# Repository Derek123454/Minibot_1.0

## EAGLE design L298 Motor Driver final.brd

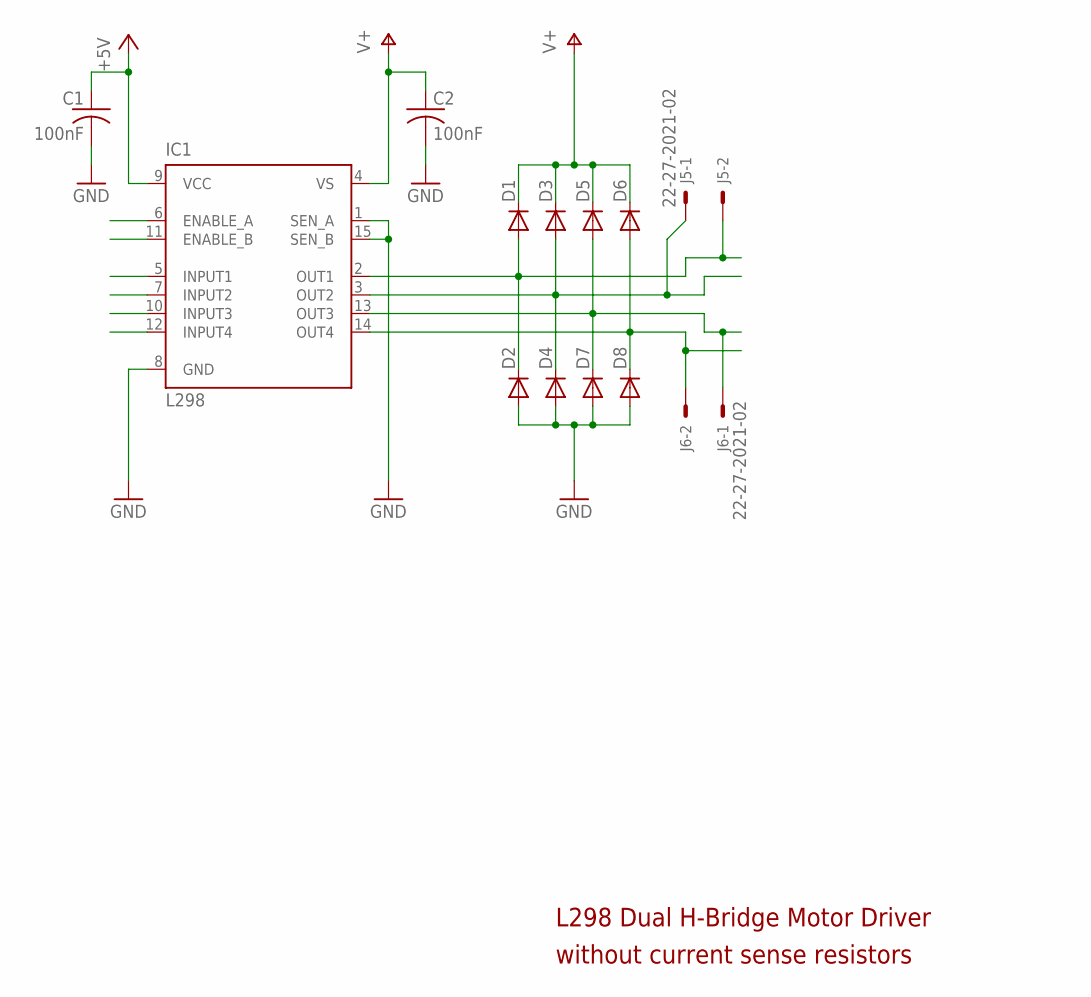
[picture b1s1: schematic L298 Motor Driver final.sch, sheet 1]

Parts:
C1, C2: 100nF; C050-024X044
D1, D2, D3, D4, D5, D6, D7, D8: DIODE-D-5; D-5
IC1: L298; MULTIWATT-15
J5, J6: 22-27-2021-02; 6410-02

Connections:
+5V: C1.1, IC1.9 (VCC); also elsewhere on the board
GND: C1.2, C2.2, D2.A, D4.A, D7.A, D8.A, IC1.1 (SEN_A), IC1.8 (GND), IC1.15 (SEN_B); also elsewhere on the board
GPIO12: IC1.6 (ENABLE_A); also elsewhere on the board
GPIO16: IC1.11 (ENABLE_B); also elsewhere on the board
GPIO19: IC1.12 (INPUT4); also elsewhere on the board
GPIO20: IC1.5 (INPUT1); also elsewhere on the board
GPIO21: IC1.7 (INPUT2); also elsewhere on the board
GPIO26: IC1.10 (INPUT3); also elsewhere on the board
unnamed: D1.A, D2.C, IC1.2 (OUT1), J5.2
unnamed: D3.A, D4.C, IC1.3 (OUT2), J5.1
unnamed: D6.A, D8.C, IC1.14 (OUT4), J6.2
unnamed: D5.A, D7.C, IC1.13 (OUT3), J6.1
V+: C2.1, D1.C, D3.C, D5.C, D6.C, IC1.4 (VS); also elsewhere on the board

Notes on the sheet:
L298 Dual H-Bridge Motor Driver
without current sense resistors

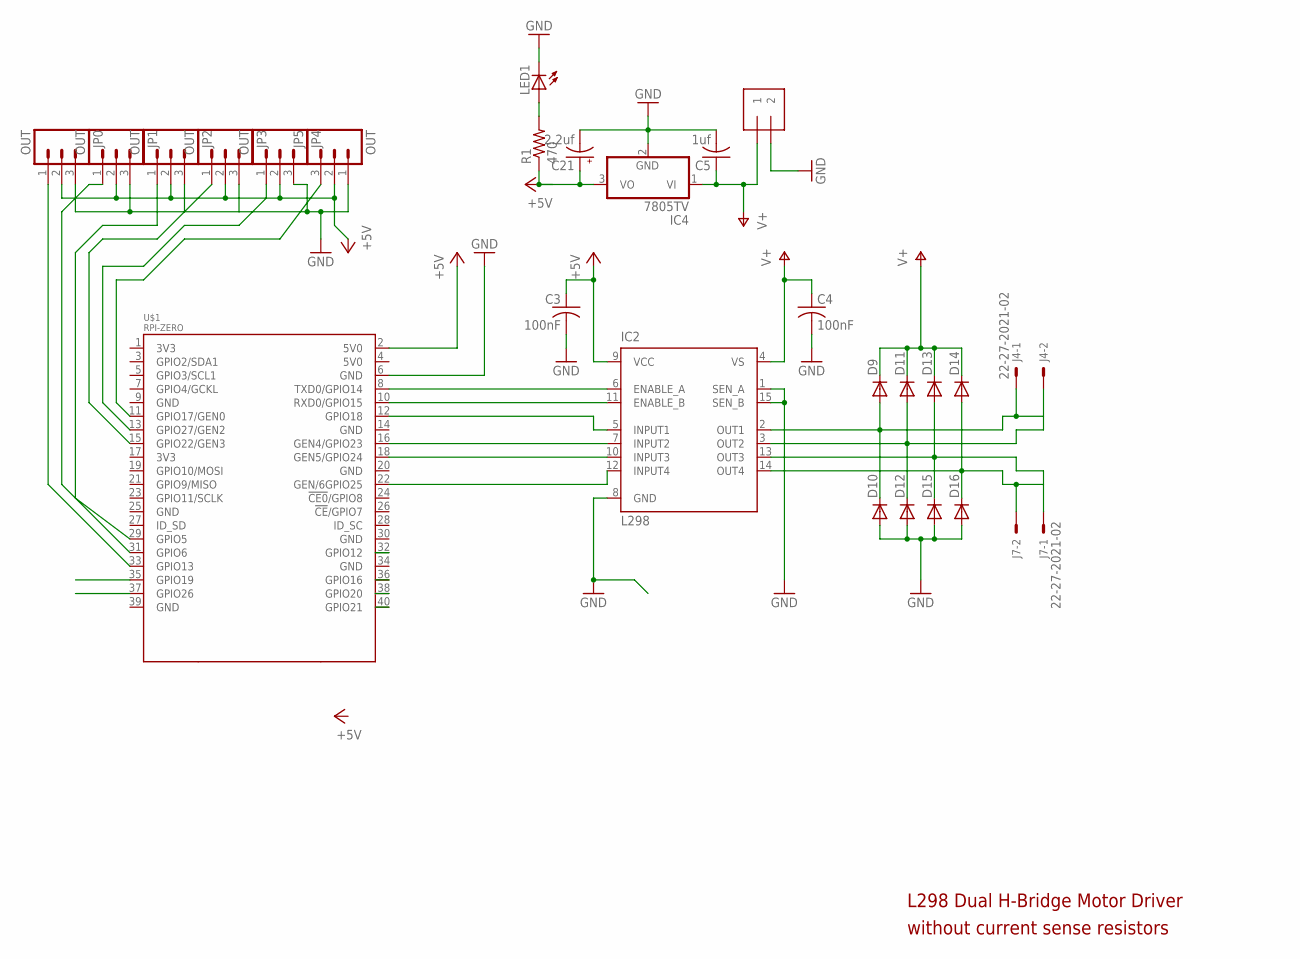
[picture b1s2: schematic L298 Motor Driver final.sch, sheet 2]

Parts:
C3, C4: 100nF; C050-024X044
C5: 1uf; C050-024X044
C21: 2.2uf; E1,8-4
D9, D10, D11, D12, D13, D14, D15, D16: DIODE-D-5; D-5
IC2: L298; MULTIWATT-15
IC4: 7805TV; TO220V
J1: 1X2-3.5MM
J4, J7: 22-27-2021-02; 6410-02
JP0, JP1, JP2, JP3, JP4, JP5: OUT; 1X03
LED1: LED5MM
R1: 470; 0204/7
U$1: RPI-ZERO; RASPBERRYPI_BASTELSTUBE_V13_RASPI_BOARD_B+_FULL

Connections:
+5V: C3.1, C21.+, IC2.9 (VCC), IC4.3 (VO), JP0.2, JP1.2, JP2.2, JP3.2, JP4.2, JP5.2, R1.1, U$1.2 (5V0); also elsewhere on the board
GND: C3.2, C4.2, C5.2, C21.-, D10.A, D12.A, D15.A, D16.A, IC2.1 (SEN_A), IC2.8 (GND), IC2.15 (SEN_B), IC4.2 (GND), J1.2, JP0.3, JP1.3, JP2.3, JP3.3, JP4.3, JP5.1, LED1.K (C), U$1.6 (GND); also elsewhere on the board
GPIO12: U$1.32 (GPIO12); also elsewhere on the board
GPIO16: U$1.36 (GPIO16); also elsewhere on the board
GPIO19: U$1.35 (GPIO19); also elsewhere on the board
GPIO20: U$1.38 (GPIO20); also elsewhere on the board
GPIO21: U$1.40 (GPIO21); also elsewhere on the board
GPIO26: U$1.37 (GPIO26); also elsewhere on the board
unnamed: LED1.A, R1.2
unnamed: JP0.1, U$1.33 (GPIO13)
unnamed: JP1.1, U$1.31 (GPIO6)
unnamed: JP2.1, U$1.29 (GPIO5)
unnamed: JP3.1, U$1.15 (GPIO22/GEN3)
unnamed: D9.A, D10.C, IC2.2 (OUT1), J4.1
unnamed: D11.A, D12.C, IC2.3 (OUT2), J4.2
unnamed: D14.A, D16.C, IC2.14 (OUT4), J7.2
unnamed: D13.A, D15.C, IC2.13 (OUT3), J7.1
unnamed: IC2.6 (ENABLE_A), U$1.8 (TXD0/GPIO14)
unnamed: IC2.11 (ENABLE_B), U$1.10 (RXD0/GPIO15)
unnamed: IC2.5 (INPUT1), U$1.12 (GPIO18)
unnamed: IC2.7 (INPUT2), U$1.16 (GEN4/GPIO23)
unnamed: IC2.10 (INPUT3), U$1.18 (GEN5/GPIO24)
unnamed: IC2.12 (INPUT4), U$1.22 (GEN/6GPIO25)
unnamed: JP4.1, U$1.13 (GPIO27/GEN2)
unnamed: JP5.3, U$1.11 (GPIO17/GEN0)
V+: C4.1, C5.1, D9.C, D11.C, D13.C, D14.C, IC2.4 (VS), IC4.1 (VI), J1.1; also elsewhere on the board

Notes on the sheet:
L298 Dual H-Bridge Motor Driver
without current sense resistors

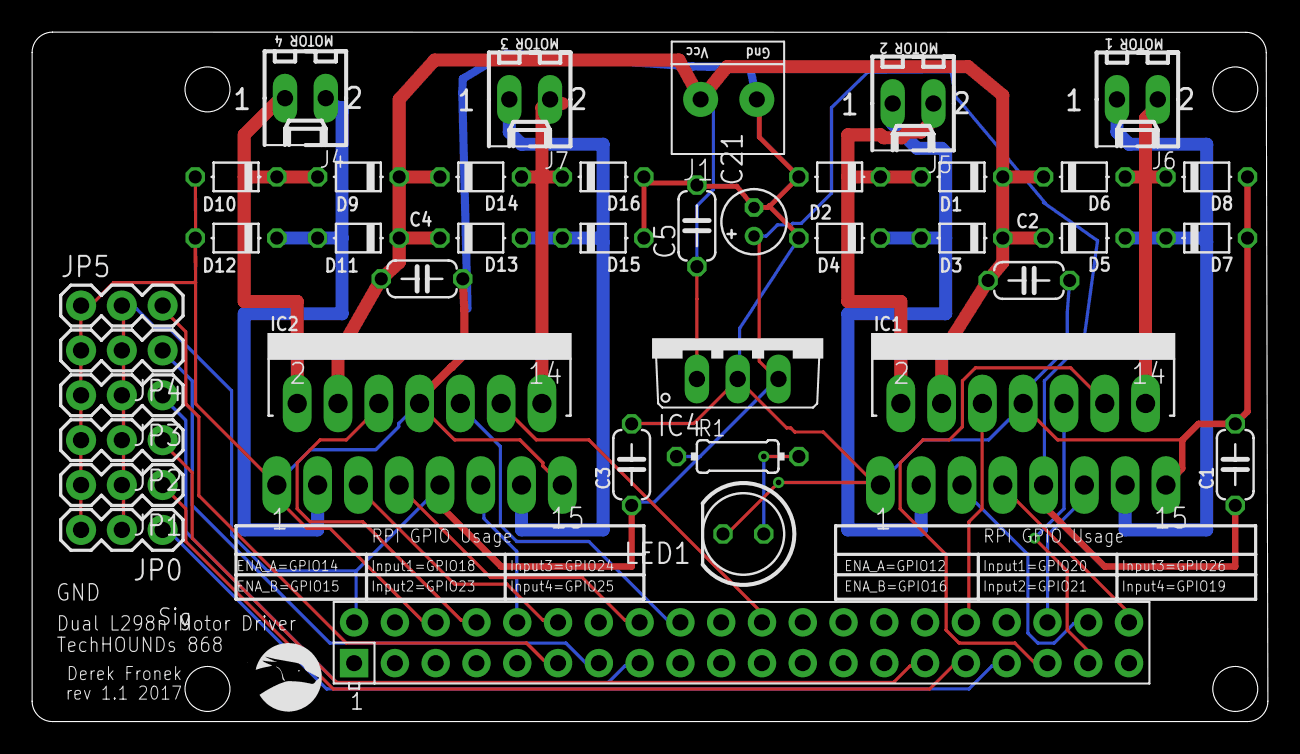
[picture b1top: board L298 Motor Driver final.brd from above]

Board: 2 copper layers, 77.0 x 42.9 mm, 39 parts (0 on the bottom side), 30 nets.

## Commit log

2017-12-03 Add files via upload
    For Webiopi Minibots
2017-12-04 Add Servo Control
2017-12-04 Add Fix-Width PWM Servo Control
2017-12-04 Fix Webpage Macro Calls
2017-12-04 Make PWM Signal Once
